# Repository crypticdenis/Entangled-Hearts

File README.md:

The goal is a slim, fully self-contained touch screen device on a custom PCB that can be charged and programmed via a single USB-C port.

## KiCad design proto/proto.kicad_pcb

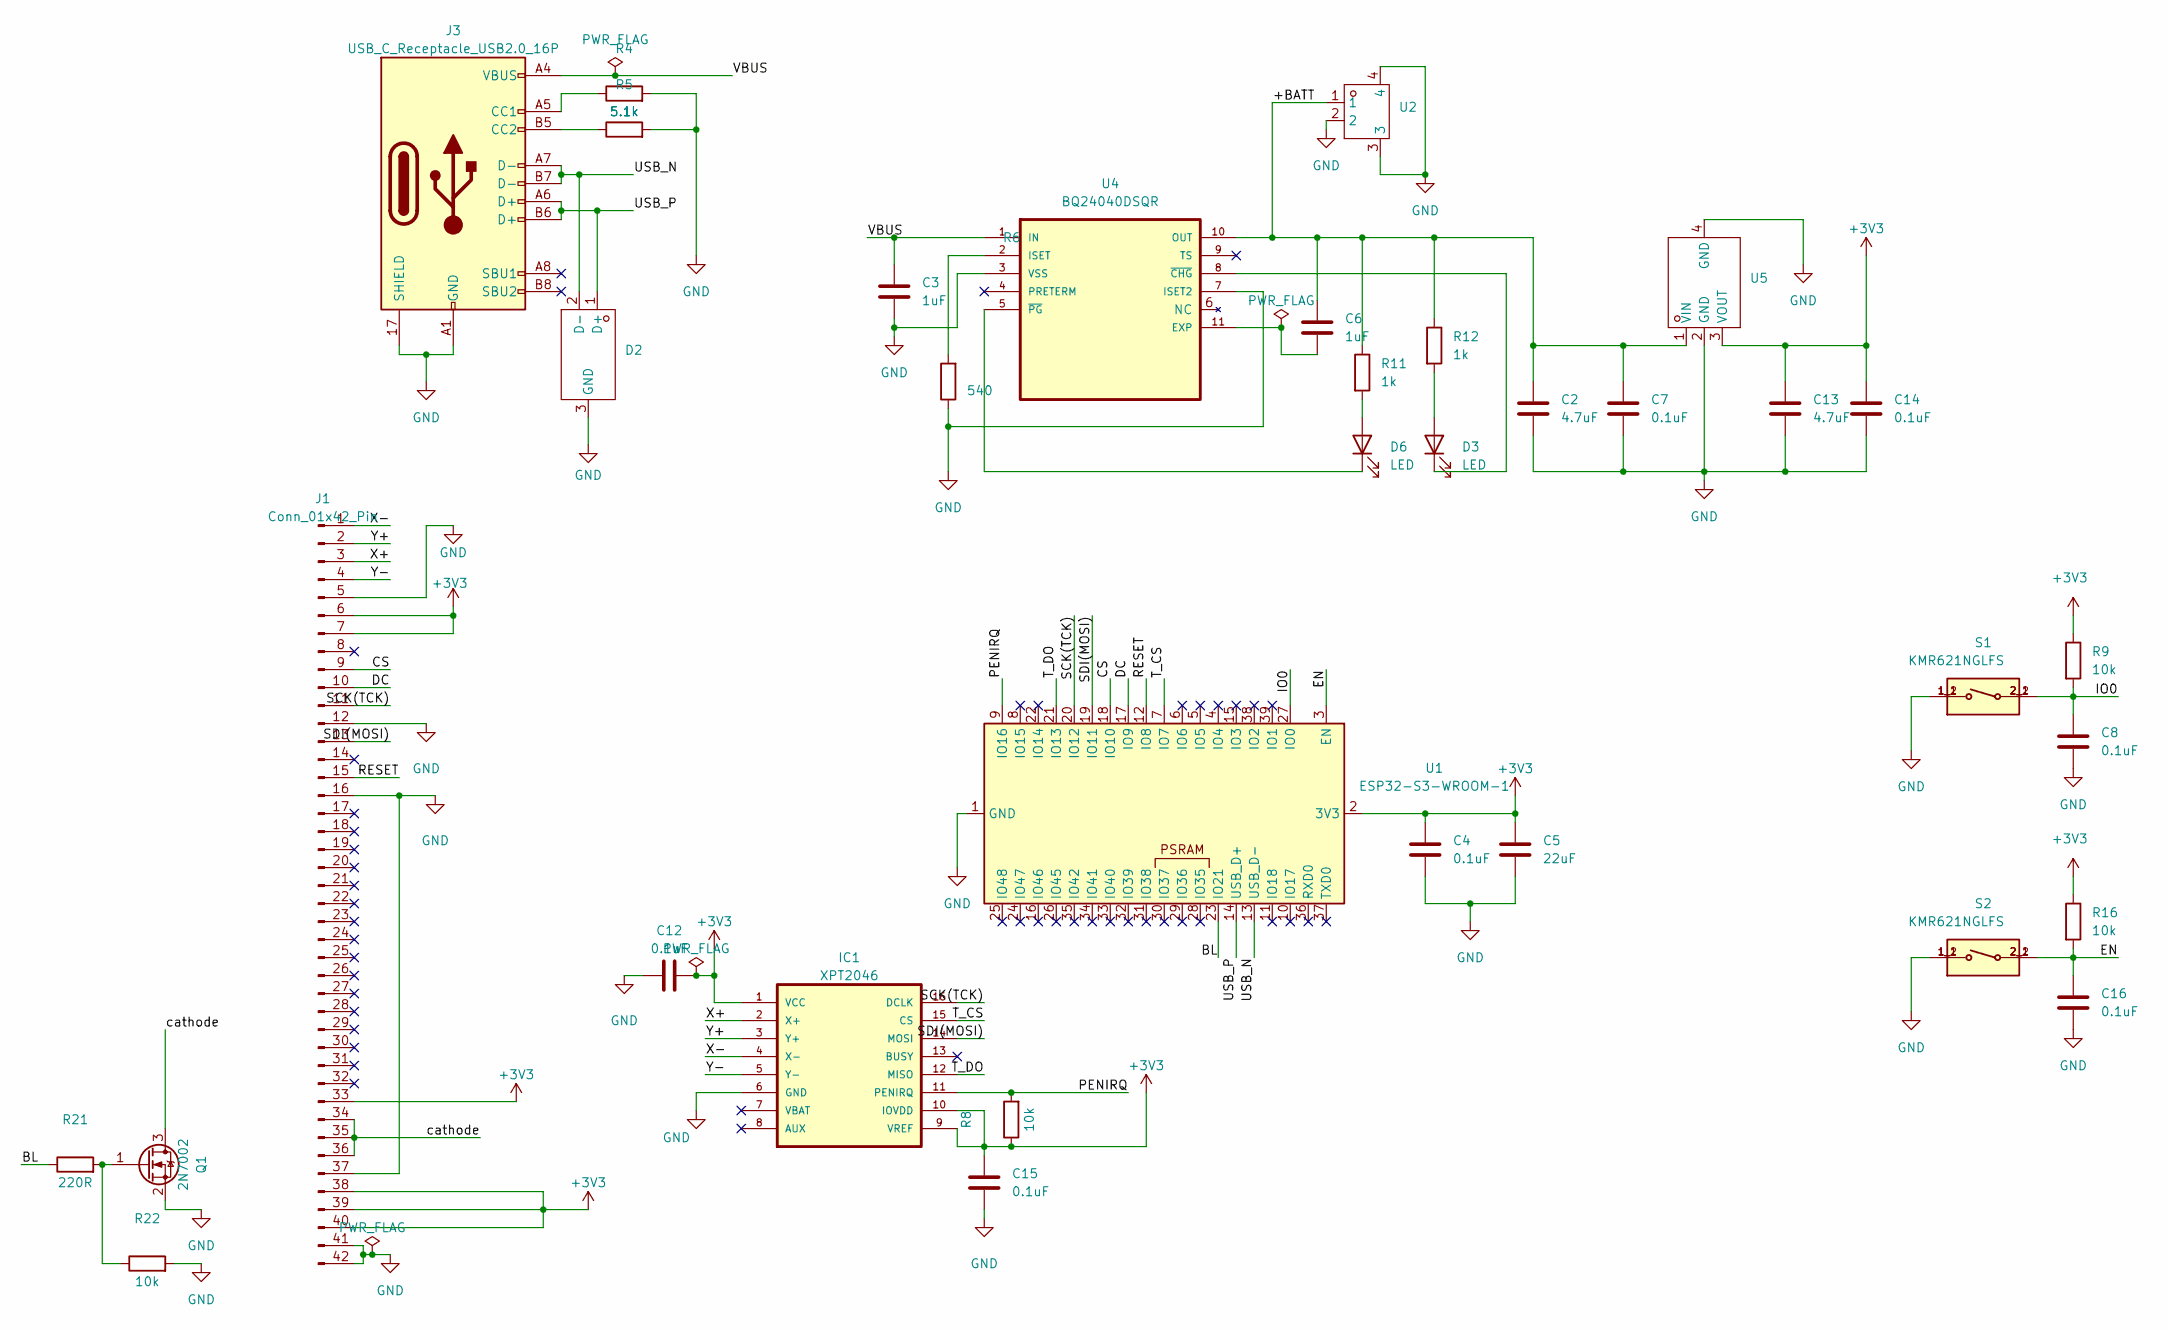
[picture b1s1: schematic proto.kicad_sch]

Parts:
C2, C13: 4.7uF; C_0603_1608Metric
C3, C6: 1uF; C_0603_1608Metric
C4, C7, C8, C12, C14, C15, C16: 0.1uF; C_0603_1608Metric
C5: 22uF; C_0603_1608Metric
D2: SOT-723; Manufacturer Part TPD2EUSB30DRTR-TP; LCSC Part Name TPD2EUSB30DRTR-TP
D3, D6: LED; LED_0805_2012Metric
IC1: XPT2046; TSSOP16
J1: Conn_01x42_Pin; FFC-SMD_FFC05001-40SBB124W5M
J3: USB_C_Receptacle_USB2.0_16P; USB-C-SMD_TYPE-C-31-M-08A
Q1: 2N7002; SOT-23
R4, R5: 5.1k; R_0603_1608Metric
R6: 540; R_0603_1608Metric
R8, R9, R16, R22: 10k; R_0603_1608Metric
R11, R12: 1k; R_0603_1608Metric
R21: 220R; R_0603_1608Metric
S1, S2: KMR621NGLFS; SW_KMR621NGLFS; PARTREV N/A
U1: ESP32-S3-WROOM-1
U2: CONN-SMD_ZX-PH2.0-WT2P; Manufacturer Part ZX-PH2.0-WT2P; LCSC Part Name 1x2P 间距:2mm 卧贴 系列:PH 配套胶壳型号：ZX-PH2.0-2P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
U4: BQ24040DSQR; SON40P200X200X80-11N
U5: SOT-223-3_L6.7-W3.7-P2.30-LS7.0-BR; Manufacturer Part MCP1826S-3302E/DB; LCSC Part Name MCP1826S-3302E/DB

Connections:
+3V3: C4.1, C5.1, C12.2, C13.1, C14.1, C15.2, IC1.1 (VCC), IC1.9 (VREF), IC1.10 (IOVDD), J1.6, J1.7, J1.33, J1.38, J1.39, J1.40, R8.1, R9.1, R16.1, U1.2 (3V3), U5.3 (VOUT)
/+BATT: C2.1, C6.1, C7.1, R11.1, R12.1, U2.1, U4.10 (OUT), U5.1 (VIN)
/BL: R21.1, U1.23 (IO21)
/CS: J1.9, U1.18 (IO10)
/DC: J1.10, U1.17 (IO9)
/EN: C16.2, R16.2, S2.2_1, S2.2_2, U1.3 (EN)
/IO0: C8.2, R9.2, S1.2_1, S1.2_2, U1.27 (IO0)
/PENIRQ: IC1.11 (PENIRQ), R8.2, U1.9 (IO16)
/RESET: J1.15, U1.12 (IO8)
/SCK(TCK): IC1.16 (DCLK), J1.11, U1.20 (IO12)
/SDI(MOSI): IC1.14 (MOSI), J1.13, U1.19 (IO11)
/T_CS: IC1.15 (CS), U1.7 (IO7)
/T_DO: IC1.12 (MISO), U1.21 (IO13)
/USB_N: D2.2 (D-), J3.A7 (D-), J3.B7 (D-), U1.13 (USB_D-)
/USB_P: D2.1 (D+), J3.A6 (D+), J3.B6 (D+), U1.14 (USB_D+)
/VBUS: C3.1, J3.A4 (VBUS), J3.A9 (VBUS), J3.B4 (VBUS), J3.B9 (VBUS), U4.1 (IN)
/X+: IC1.2 (X+), J1.3
/X-: IC1.4 (X-), J1.1
/Y+: IC1.3 (Y+), J1.2
/Y-: IC1.5 (Y-), J1.4
/cathode: J1.34, J1.35, J1.36, Q1.3 (D)
GND: C2.2, C3.2, C4.2, C5.2, C7.2, C8.1, C12.1, C13.2, C14.2, C15.1, C16.1, D2.3 (GND), IC1.6 (GND), J1.5, J1.12, J1.16, J1.37, J1.41, J1.42, J3.17 (SHIELD), J3.18 (SHIELD), J3.19 (SHIELD), J3.20 (SHIELD), J3.A1 (GND), J3.A12 (GND), J3.B1 (GND), J3.B12 (GND), Q1.2 (S), R4.2, R5.2, R6.1, R22.2, S1.1_1, S1.1_2, S2.1_1, S2.1_2, U1.1 (GND), U1.40 (GND), U1.41 (GND), U2.2, U2.3, U2.4, U4.3 (VSS), U4.7 (ISET2), U5.2 (GND), U5.4 (GND)
unnamed: D3.2 (A), R12.2
unnamed: D3.1 (K), U4.8 (~CHG)
unnamed: D6.2 (A), R11.2
unnamed: D6.1 (K), U4.5 (~PG)
unnamed: J3.A5 (CC1), R4.1
unnamed: J3.B5 (CC2), R5.1
unnamed: Q1.1 (G), R21.2, R22.1
unnamed: C6.2, U4.11 (EXP)
unnamed: R6.2, U4.2 (ISET)

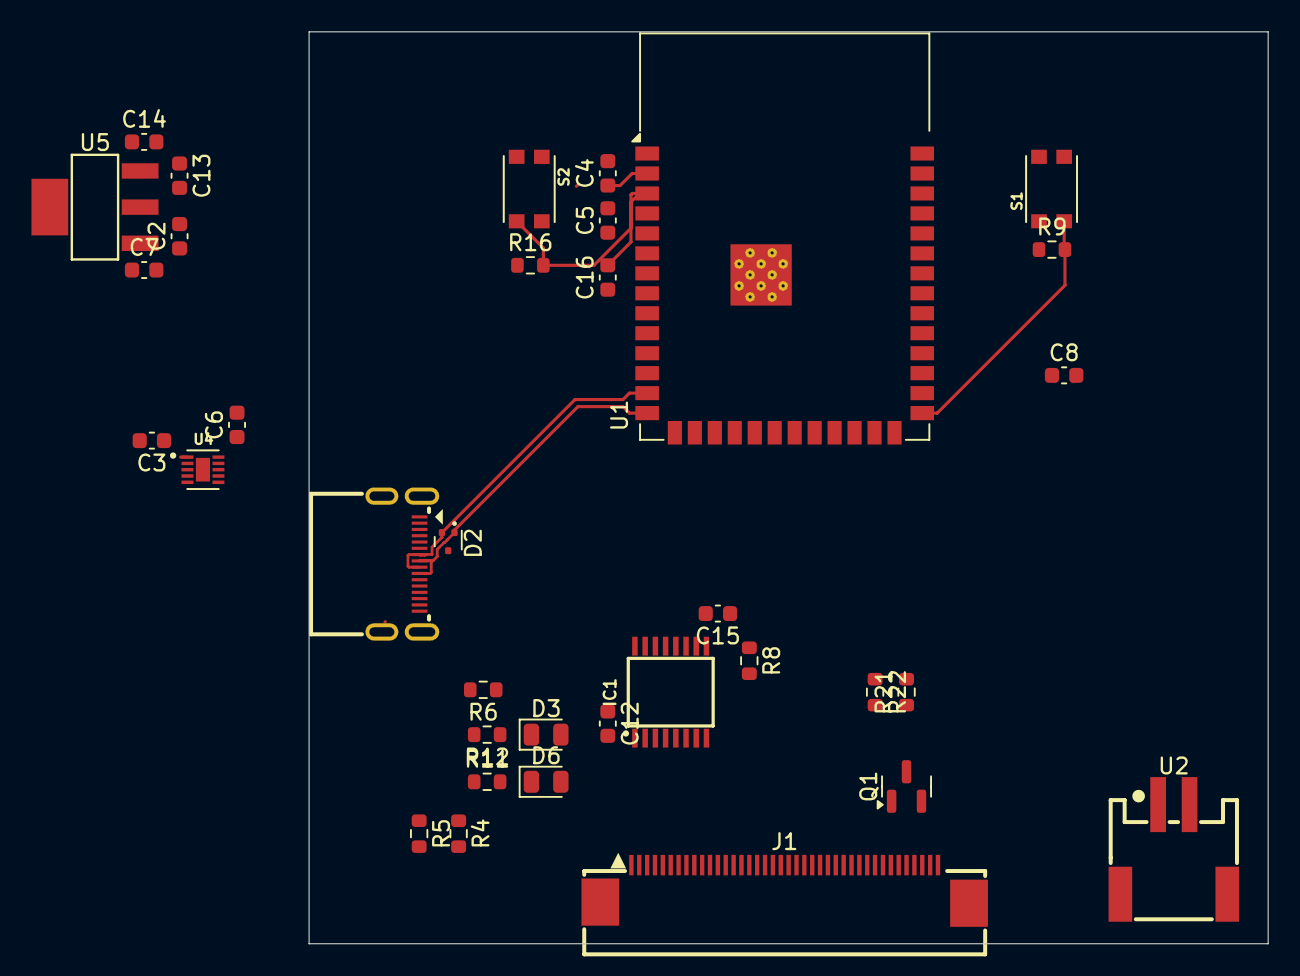
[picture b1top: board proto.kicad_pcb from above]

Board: 2 copper layers, 61.0 x 58.0 mm, 35 parts (0 on the bottom side), 31 nets.
